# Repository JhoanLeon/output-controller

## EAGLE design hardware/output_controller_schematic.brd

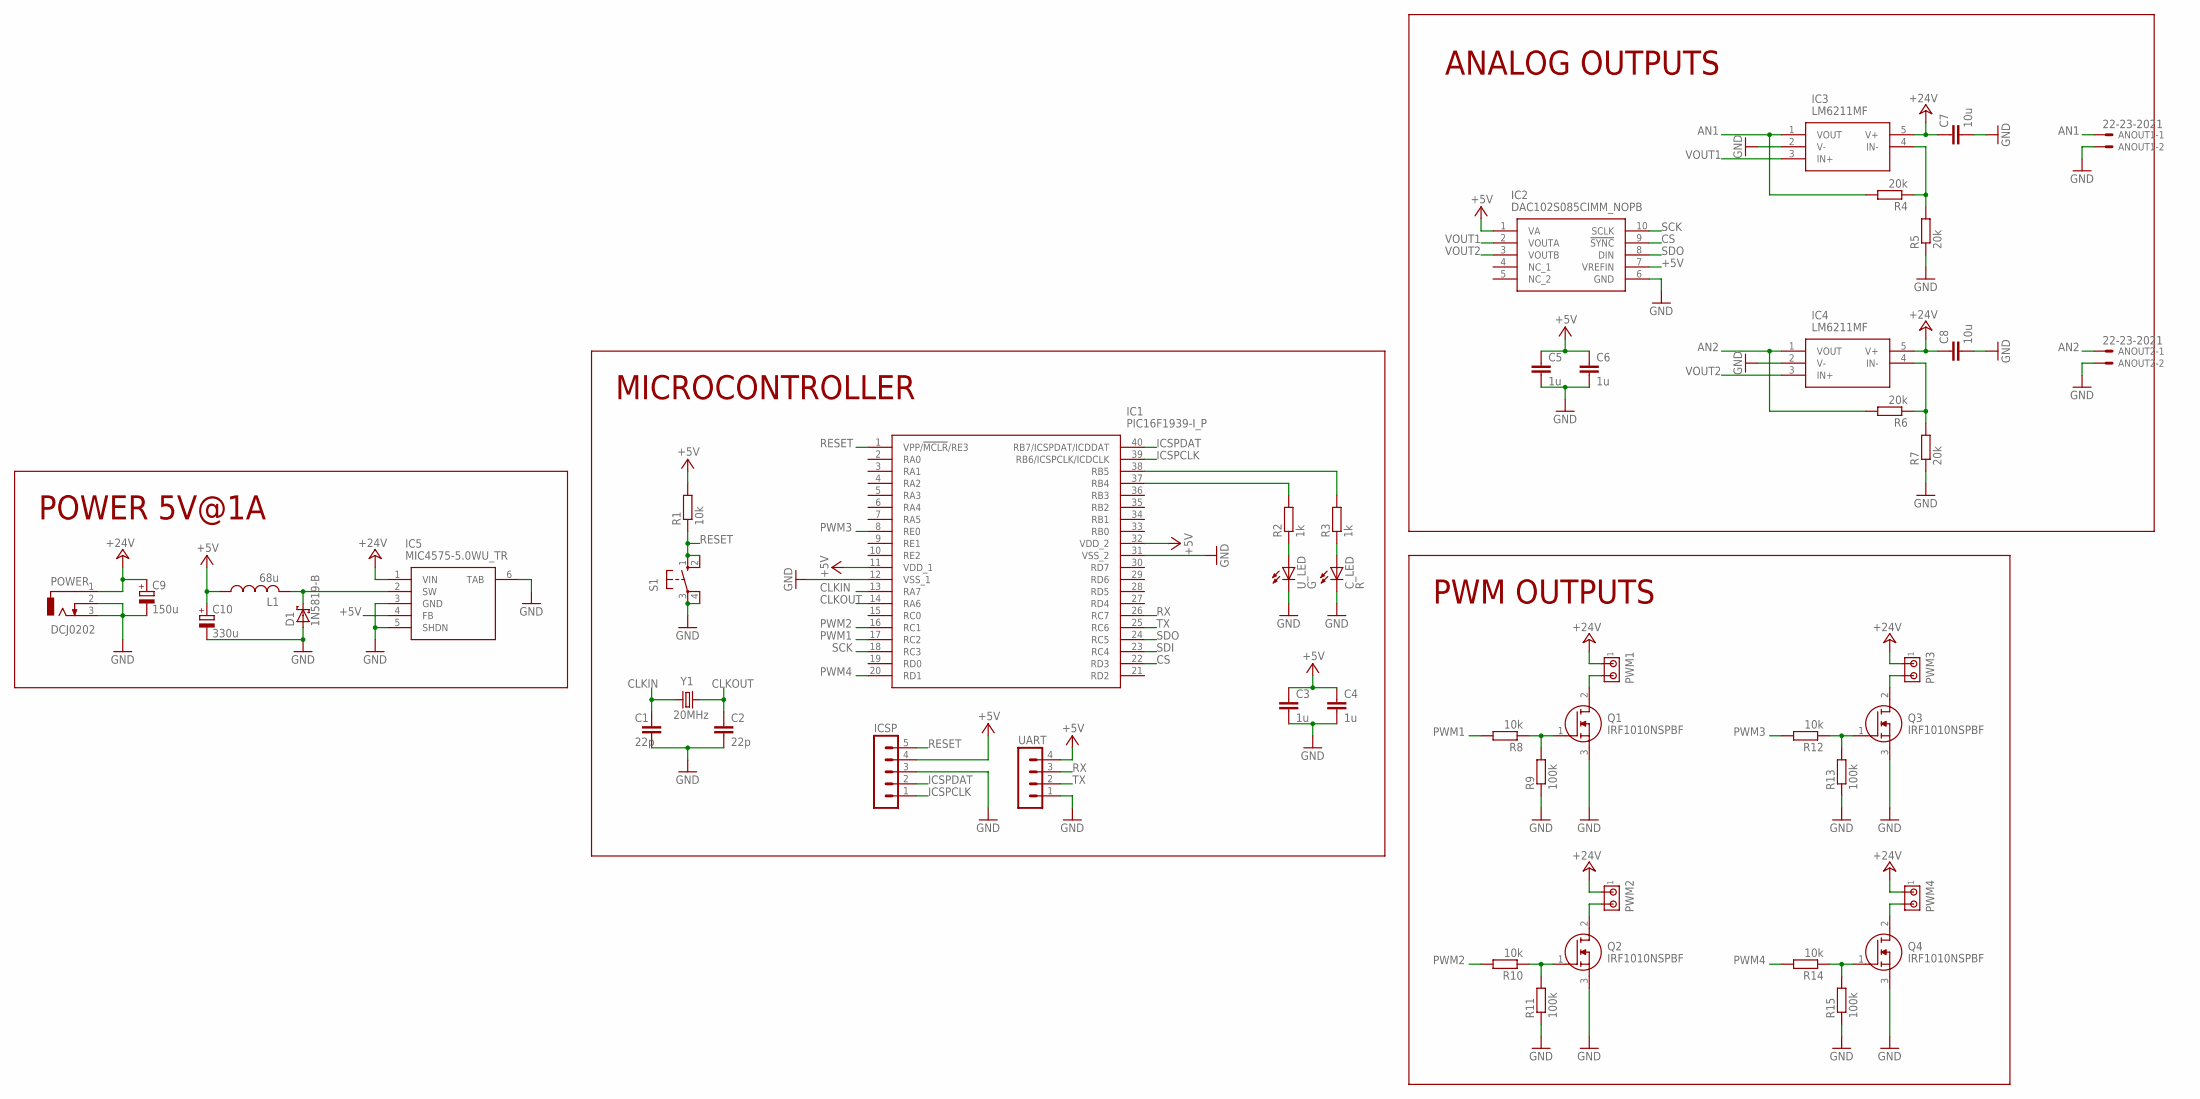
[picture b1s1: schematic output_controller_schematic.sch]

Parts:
ANOUT1, ANOUT2: 22-23-2021
C1, C2: 22p; C1206
C3, C4, C5, C6: 1u; C1206
C7, C8: 10u; C1206
C9: 150u; 175TMP-0810
C10: 330u; 175TMP-0810
C_LED: R; CHIPLED_1206
D1: 1N5819-B; DO41-7.6
IC1: PIC16F1939-I_P; DIP1543W58P254L5175H635Q40N
IC2: DAC102S085CIMM_NOPB; SOP50P490X110-10N
IC3, IC4: LM6211MF; SOT95P284X122-5N
IC5: MIC4575-5.0WU_TR; MIC2930112WU
ICSP: MA05-1
L1: 68u; L5650M
POWER: DCJ0202
PWM1, PWM2, PWM3, PWM4: MTA02-156; 1X2MTA
Q1, Q2, Q3, Q4: IRF1010NSPBF; IRF2804STRLPBF
R1, R8, R10, R12, R14: 10k; R1206
R2, R3: 1k; R1206
R4, R5, R6, R7: 20k; R1206
R9, R11, R13, R15: 100k; R1206
S1: 10-XX; B3F-10XX
UART: MA04-1
U_LED: G; CHIPLED_1206
Y1: 20MHz; HC49/S

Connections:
+5V: C3.1, C4.1, C5.1, C6.1, C10.+, IC1.11 (VDD_1), IC1.32 (VDD_2), IC2.1 (VA), IC2.7 (VREFIN), IC5.4 (FB), ICSP.4, L1.1, R1.2, UART.4
+24V: C7.1, C8.1, C9.+, IC3.5 (V+), IC4.5 (V+), IC5.1 (VIN), POWER.1, PWM1.1, PWM2.1, PWM3.1, PWM4.1
AN1: ANOUT1.1, IC3.1 (VOUT), R4.2
AN2: ANOUT2.1, IC4.1 (VOUT), R6.2
CLKIN: C1.1, IC1.13 (RA7), Y1.1
CLKOUT: C2.1, IC1.14 (RA6), Y1.2
CS: IC1.22 (RD3), IC2.9 (!SYNC)
GND: ANOUT1.2, ANOUT2.2, C1.2, C2.2, C3.2, C4.2, C5.2, C6.2, C7.2, C8.2, C9.-, C10.-, C_LED.C, D1.A, IC1.12 (VSS_1), IC1.31 (VSS_2), IC2.6 (GND), IC3.2 (V-), IC4.2 (V-), IC5.3 (GND), IC5.5 (SHDN), IC5.6 (TAB), ICSP.3, POWER.2, POWER.3, Q1.3 (S), Q2.3 (S), Q3.3 (S), Q4.3 (S), R5.1, R7.1, R9.1, R11.1, R13.1, R15.1, S1.3, S1.4 (P1), UART.1, U_LED.C
ICSPCLK: IC1.39 (RB6/ICSPCLK/ICDCLK), ICSP.1
ICSPDAT: IC1.40 (RB7/ICSPDAT/ICDDAT), ICSP.2
unnamed: IC3.4 (IN-), R4.1, R5.2
unnamed: IC4.4 (IN-), R6.1, R7.2
unnamed: IC1.38 (RB5), R3.2
unnamed: IC1.37 (RB4), R2.2
unnamed: R2.1, U_LED.A
unnamed: C_LED.A, R3.1
unnamed: Q1.1 (G), R8.1, R9.2
unnamed: PWM1.2, Q1.2 (D)
unnamed: Q2.1 (G), R10.1, R11.2
unnamed: PWM2.2, Q2.2 (D)
unnamed: Q3.1 (G), R12.1, R13.2
unnamed: PWM3.2, Q3.2 (D)
unnamed: Q4.1 (G), R14.1, R15.2
unnamed: PWM4.2, Q4.2 (D)
unnamed: D1.C, IC5.2 (SW), L1.2
PWM1: IC1.17 (RC2), R8.2
PWM2: IC1.16 (RC1), R10.2
PWM3: IC1.8 (RE0), R12.2
PWM4: IC1.20 (RD1), R14.2
RESET: IC1.1 (VPP/!MCLR!/RE3), ICSP.5, R1.1, S1.1 (S), S1.2 (S1)
RX: IC1.26 (RC7), UART.3
SCK: IC1.18 (RC3), IC2.10 (SCLK)
SDI: IC1.23 (RC4)
SDO: IC1.24 (RC5), IC2.8 (DIN)
TX: IC1.25 (RC6), UART.2
VOUT1: IC2.2 (VOUTA), IC3.3 (IN+)
VOUT2: IC2.3 (VOUTB), IC4.3 (IN+)

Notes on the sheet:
POWER 5V@1A
MICROCONTROLLER
ANALOG OUTPUTS
PWM OUTPUTS

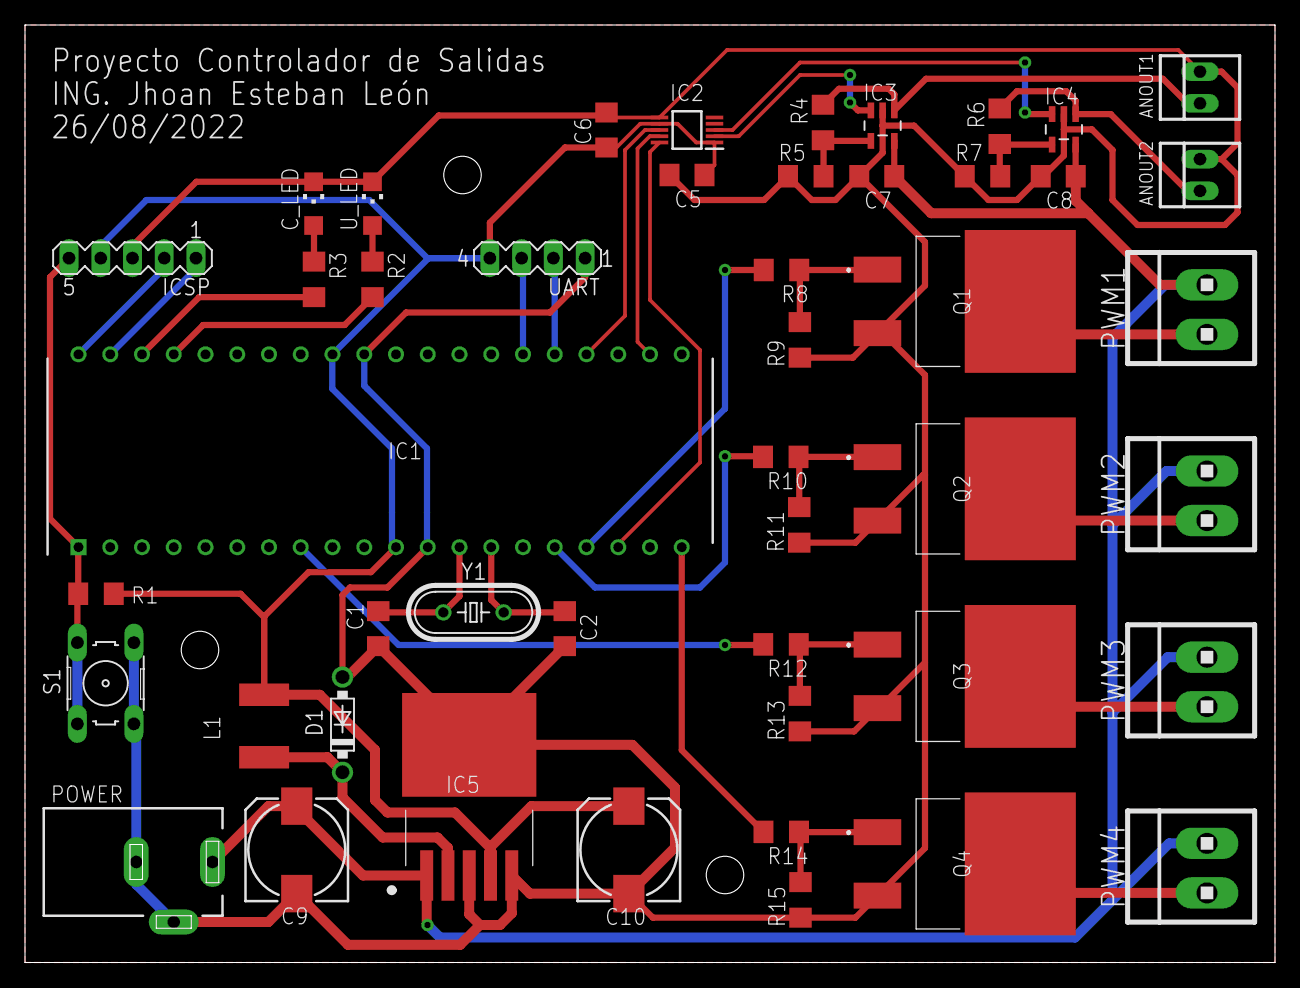
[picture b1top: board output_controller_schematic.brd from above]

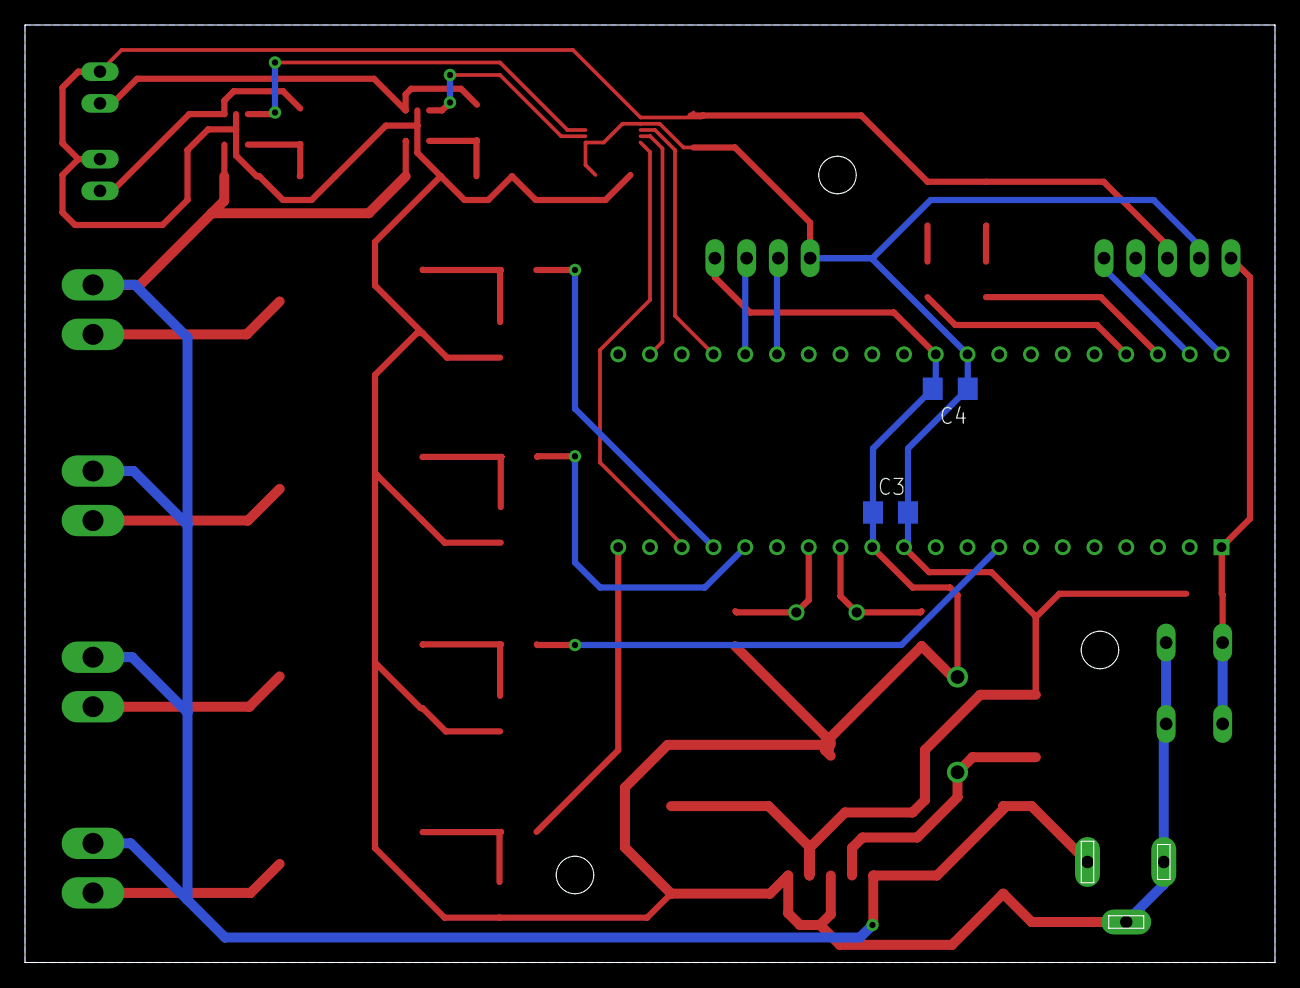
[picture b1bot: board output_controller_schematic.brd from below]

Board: 2 copper layers, 100.0 x 75.0 mm, 49 parts (2 on the bottom side), 36 nets.

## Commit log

2022-08-23 First steps in schematic design
2022-08-23 documentation and anouts added
2022-08-23 pwm outputs completed
2022-08-24 complete schematic design and PCB layout generated
2022-08-24 first uncomplete organization of PCB layout
2022-08-25 start code and simulation with blinking leds
2022-08-26 first code to PWM generation
2022-08-26 first implementation of UART communication
2022-08-27 stable working version of 90% uart protocol
2022-08-27 final working version without details
2022-08-27 final commented version of code
2022-12-09 adding final files
